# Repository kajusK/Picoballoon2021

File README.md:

Picoballoon Challenge 2021, Deadbadger probe
============================================

This probe was designed [Picoballoon Challenge](https://www.hvezdarna.cz/novinky/picoballoon-challenge-2021/)
organised by Brno Observatory and Planetarium. A goal of this competition
is to make a probe under 20 grams that would be launched on ballon to altitudes
around 5-15 km. Only requirement except weight is sending current altitude of the probe.

A detailed description is available at [deadbadger.cz](https://deadbadger.cz/projects/picoballoon-2021),
tracking site is at [bal.deadbadger.cz](https://bal.deadbadger.cz).

The probe contains
  * STM32F051 MCU
  * MS5607 Pressure and temperature sensor
  * Quectel L96 GPS module with integrated antenna
  * RFM95 LoRa Transceiver
  * MCP1640 based 3.3V boost regulator

Firmware
--------
As the commonly used [LMIC](https://github.com/matthijskooijman/arduino-lmic/tree/master/src)
library is quite bulky and far from perfect, I wrote my own LoRaWan library
inspired by [TinyLoRa](https://github.com/adafruit/TinyLoRa).

The main loop does about this:
  * Power up, initialize peripherals
  * Measure system voltages, pressure
  * Wait for GPS data or timeout
  * Power off GPS
  * Send data over LoRa (ABP, unconfirmed uplink)
  * Power off RFM95 trancesiver
  * Power off for 30 minutes
  * Repeat (GPS is powered on every 4th cycle)

Hardware
--------
The board was designed for 0.6 mm thick two sided PCB to reduce weight as
much as possible. Using thicker boards (usually 1.6 mm) changes the antenna
trace impedance, but it should not be that significant.

The programming and debug uart connectors are separated from the main layout
and this piece of the PCB will be snapped off before launch to reduce weight.

**Power consumption** with 3 V power supply
  * board topped at 50 mA with GPS searching for satellites, RFM in standby and MCU running
  * 7,3 mA with GPS powered off
  * 5,3 mA with RFM95 in sleep mode and GPS off
  * 45 uA with devices powered off

**Weight**
  * 10 g - Battery
  * ~3 g - Probe PCB with programming header
  * 12,39 g - Take off weight, officially measured

Frontend
--------
Data received by [TTN](https://www.thethingsnetwork.org/) are sent over
HTTP integration to custom web server that verifies the
auth header and stores data in sqlite database.

User frontend is written in python, it shows all received packets, flight route
and current position on a [map](https://api.mapy.cz).
The tracker is available at [bal.deadbadger](https://bal.deadbadger.cz)

To run the frontend in docker, run
```
docker build -t picoballon .
mkdir /srv/probe
touch /srv/probe/database.sqlite
# set token to use in auth header
echo "someuser:somepassword" > /srv/probe/token.txt
docker run -v /srv/probe/data:/project/cloud_data --mount type=bind,source=/srv/probe/database.sqlite,target=/project/database.sqlite --mount type=bind,source=/srv/probe/credentials.txt,target=/project/credentials.txt -p 8081:80 --name picoballon -d picoballon
```

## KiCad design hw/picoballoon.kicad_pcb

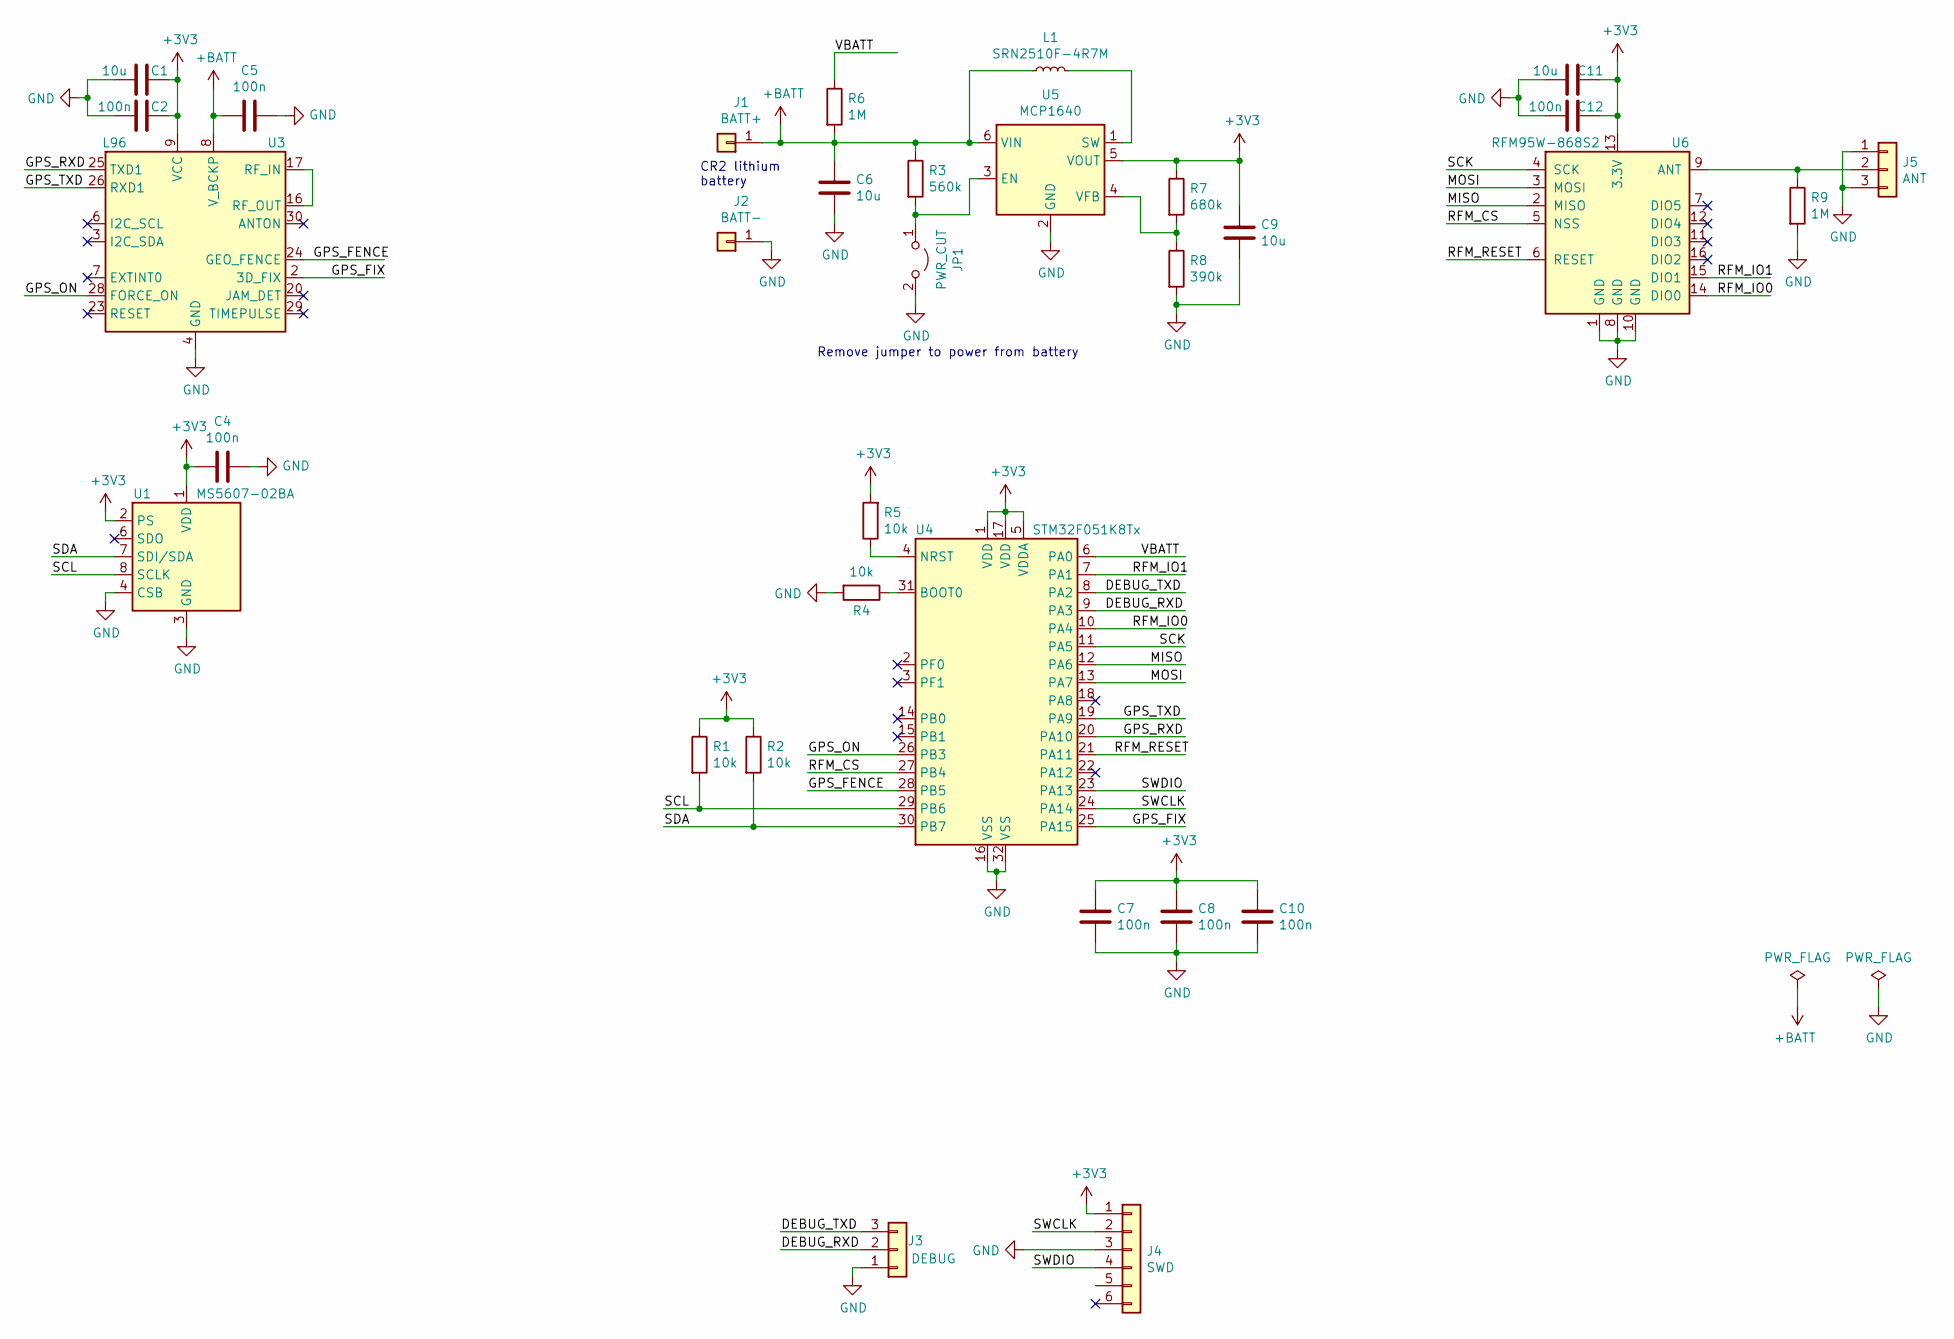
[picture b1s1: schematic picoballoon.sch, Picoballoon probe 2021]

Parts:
C1, C6, C9, C11: 10u; C_0603_1608Metric
C2, C4, C5, C7, C8, C10, C12: 100n; C_0603_1608Metric
J1: BATT+; PinSocket_1x01_P2.54mm_Vertical
J2: BATT-; PinHeader_1x01_P2.54mm_Vertical
J3: DEBUG; PinHeader_1x03_P2.54mm_Vertical
J4: SWD; PinHeader_2x03_P1.27mm_Vertical_SMD
J5: ANT; PinHeader_1x03_P2.54mm_Vertical
JP1: PWR_CUT; SolderJumper-2_P1.3mm_Open_Pad1.0x1.5mm
L1: SRN2510F-4R7M; L_Abracon_ASPI-3012S
R1, R2, R4, R5: 10k; R_0603_1608Metric
R3: 560k; R_0603_1608Metric
R6, R9: 1M; R_0603_1608Metric
R7: 680k; R_0603_1608Metric
R8: 390k; R_0603_1608Metric
U1: MS5607-02BA; LGA-8_3x5mm_P1.25mm
U3: L96; Quectel_L96
U4: STM32F051K8Tx; LQFP-32_7x7mm_P0.8mm
U5: MCP1640; SOT-23-6
U6: RFM95W-868S2; HOPERF_RFM9XW_SMD

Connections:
+3V3: C1.1, C2.1, C4.2, C7.1, C8.1, C9.1, C10.1, C11.1, C12.1, J4.1, R1.1, R2.1, R5.2, R7.1, U1.1 (VDD), U1.2 (PS), U3.9 (VCC), U4.1 (VDD), U4.5 (VDDA), U4.17 (VDD), U5.5 (VOUT), U6.13 (3.3V)
+BATT: C5.2, C6.1, J1.1, L1.1, R3.1, R6.2, U3.8 (V_BCKP), U3.23 (RESET), U5.6 (VIN)
/DEBUG_RXD: J3.2, U4.9 (PA3)
/DEBUG_TXD: J3.3, U4.8 (PA2)
/GPS_FENCE: U3.24 (GEO_FENCE), U4.28 (PB5)
/GPS_FIX: U3.2 (3D_FIX), U4.25 (PA15)
/GPS_ON: U3.28 (FORCE_ON), U4.26 (PB3)
/GPS_RXD: U3.25 (TXD1), U4.20 (PA10)
/GPS_TXD: U3.26 (RXD1), U4.19 (PA9)
/MISO: U4.12 (PA6), U6.2 (MISO)
/MOSI: U4.13 (PA7), U6.3 (MOSI)
/RFM_CS: U4.27 (PB4), U6.5 (NSS)
/RFM_IO0: U4.10 (PA4), U6.14 (DIO0)
/RFM_IO1: U4.7 (PA1), U6.15 (DIO1)
/RFM_RESET: U4.21 (PA11), U6.6 (RESET)
/SCK: U4.11 (PA5), U6.4 (SCK)
/SCL: R1.2, U1.8 (SCLK), U4.29 (PB6)
/SDA: R2.2, U1.7 (SDI/SDA), U4.30 (PB7)
/SWCLK: J4.2, U4.24 (PA14)
/SWDIO: J4.4, U4.23 (PA13)
/VBATT: R6.1, U4.6 (PA0)
GND: C1.2, C2.2, C4.1, C5.1, C6.2, C7.2, C8.2, C9.2, C10.2, C11.2, C12.2, J2.1, J3.1, J4.3, J5.1, J5.3, JP1.2 (B), R4.2, R8.2, R9.2, U1.3 (GND), U1.4 (CSB), U1.5 (CSB), U3.4 (GND), U3.5 (GND), U3.10 (GND), U3.11 (GND), U3.12 (GND), U3.13 (GND), U3.14 (GND), U3.15 (GND), U3.18 (GND), U3.19 (GND), U3.21 (GND), U3.22 (GND), U3.27 (GND), U3.31 (GND), U4.16 (VSS), U4.32 (VSS), U5.2 (GND), U6.1 (GND), U6.8 (GND), U6.10 (GND)
unnamed: J5.2, R9.1, U6.9 (ANT)
unnamed: JP1.1 (A), R3.2, U5.3 (EN)
unnamed: L1.2, U5.1 (SW)
unnamed: R4.1, U4.31 (BOOT0)
unnamed: R5.1, U4.4 (NRST)
unnamed: R7.2, R8.1, U5.4 (VFB)
unnamed: U3.16 (RF_OUT), U3.17 (RF_IN)

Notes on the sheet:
CR2 lithium battery
Remove jumper to power from battery

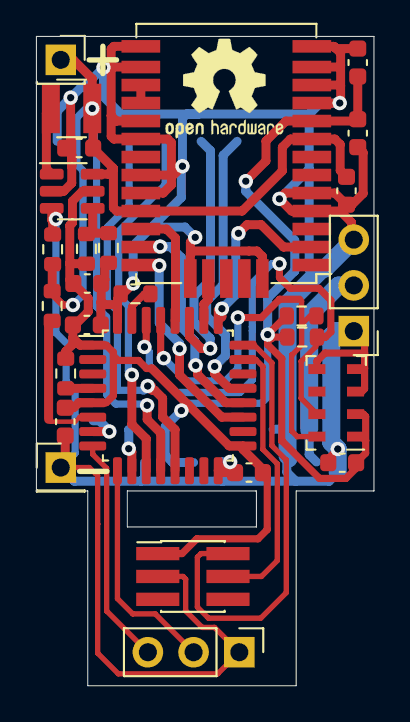
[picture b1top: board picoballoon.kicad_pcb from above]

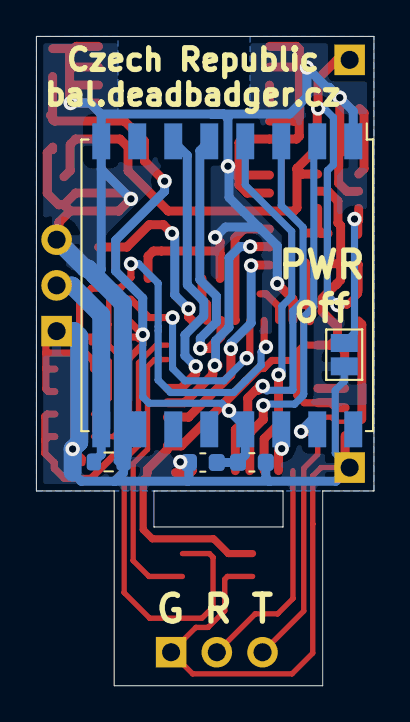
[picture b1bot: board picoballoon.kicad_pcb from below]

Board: 2 copper layers, 18.8 x 36.1 mm, 32 parts (5 on the bottom side), 29 nets.

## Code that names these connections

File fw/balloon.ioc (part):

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Mcu.Name=STM32F051K8Tx
Mcu.Package=LQFP32
Mcu.UserName=STM32F051K8Tx
PA0.GPIOParameters=GPIO_Label
PA0.GPIO_Label=VBATT
PA0.Mode=IN0
PA0.Signal=ADC_IN0
PA1.GPIOParameters=GPIO_PuPd,GPIO_Label
PA1.GPIO_Label=RFM_IO1
PA1.GPIO_PuPd=GPIO_PULLDOWN
PA1.Signal=GPIO_Input
PA10.GPIOParameters=GPIO_Label
PA10.GPIO_Label=GPS_RXD
PA10.Mode=Asynchronous
PA10.Signal=USART1_RX
PA11.GPIOParameters=GPIO_Label
PA11.GPIO_Label=RFM_RESET
PA11.Signal=GPIO_Output
PA12.Signal=GPIO_Analog
PA13.Mode=Serial_Wire
PA13.Signal=SYS_SWDIO
PA14.Mode=Serial_Wire
PA14.Signal=SYS_SWCLK
PA15.GPIOParameters=GPIO_PuPd,GPIO_Label
PA15.GPIO_Label=GPS_FIX
PA15.GPIO_PuPd=GPIO_PULLDOWN
PA15.Signal=GPIO_Input
PA2.GPIOParameters=GPIO_Label
PA2.GPIO_Label=DEBUG_TX
PA2.Mode=Asynchronous
PA2.Signal=USART2_TX
PA3.GPIOParameters=GPIO_Label
PA3.GPIO_Label=DEBUG_RX
PA3.Mode=Asynchronous
PA3.Signal=USART2_RX
PA4.GPIOParameters=GPIO_PuPd,GPIO_Label
PA4.GPIO_Label=RFM_IO0
PA4.GPIO_PuPd=GPIO_PULLDOWN
PA4.Signal=GPIO_Input
PA5.GPIOParameters=GPIO_PuPd
PA5.GPIO_PuPd=GPIO_PULLDOWN
PA5.Mode=Full_Duplex_Master
PA5.Signal=SPI1_SCK
PA6.GPIOParameters=GPIO_PuPd
PA6.GPIO_PuPd=GPIO_PULLDOWN
PA6.Mode=Full_Duplex_Master
PA6.Signal=SPI1_MISO
PA7.GPIOParameters=GPIO_PuPd
PA7.GPIO_PuPd=GPIO_PULLDOWN
PA7.Mode=Full_Duplex_Master
PA7.Signal=SPI1_MOSI
PA8.Signal=GPIO_Analog
PA9.GPIOParameters=GPIO_Label
PA9.GPIO_Label=GPS_TXD
PA9.Mode=Asynchronous
PA9.Signal=USART1_TX
PB0.Signal=GPIO_Analog
PB1.Signal=GPIO_Analog
PB3.GPIOParameters=GPIO_Label
PB3.GPIO_Label=GPS_ON
PB3.Signal=GPIO_Output
PB4.GPIOParameters=PinState,GPIO_Label
PB4.GPIO_Label=RFM_CS
PB4.PinState=GPIO_PIN_SET
PB4.Signal=GPIO_Output
PB5.GPIOParameters=GPIO_PuPd,GPIO_Label
PB5.GPIO_Label=GPS_FENCE
PB5.GPIO_PuPd=GPIO_PULLDOWN
PB5.Signal=GPIO_Input
PB6.Mode=I2C
PB6.Signal=I2C1_SCL
PB7.Mode=I2C
PB7.Signal=I2C1_SDA
PF0-OSC_IN.Signal=GPIO_Analog
PF1-OSC_OUT.Signal=GPIO_Analog
board=custom

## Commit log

2021-03-28 Added pcb design
2021-04-16 Initial firmware
2021-04-16 Added license and Readme
2021-04-23 Defined tx counter store address in linker
2021-05-09 core structure of frontend
2021-05-11 create database
2021-05-12 function endpoint, class Database in separate file db.py, create Readme
    Function database_status() checks if database.sqlite exists, if not, create one.
    Function endpoint() used for inserting data into database.
    Readme.db contains explanation of database structure.
2021-05-17 fixed creating Database instance, database attributes are now private
2021-05-17 creation of first tests
2021-05-18 added .gitignore, execute block into app.py, fixed test creating database
2021-05-22 Added TODO and tests description
2021-05-22 Rewrote the GPS timeouts and lora regions switching
2021-05-22 database path is configurable, progressing in tests of endpoint
2021-05-22 added flask context and temporary path to tests
2021-05-22 added fixtures for client and app
2021-05-22 creation of database inside class, method fetch data added
2021-05-22 function database_status removed
2021-05-22 removed test of database creation and added test of endpoint storing data
2021-05-24 added route to index.html, index contains map
    In app.py added route to index.html
    Index.html contains map centered on Brno (source: api.mapy.cz), with starting point on Brno Observatory
2021-05-25 Fixed ADC readings and sleep modes
2021-05-25 send data to markers and display them
    database instance from db.py fetch data for markers,
    index() in app.py send those data to index.html,
    which ultimately display markers with their cards to end user
2021-06-02 map can display markers using data from database
2021-06-04 display route of balloon on map
2021-06-05 latitude and longitude cannot be estimated
2021-06-05 add summary table
2021-06-07 incorporate bootstrap
    page is separated into 2 columns,
    the map has responsive size, is centered and zoomed to capture all markers, sizes of markers' cards are fixed
    sizes of the summary table and the image of probe are responsive
2021-06-07 split index() into 3 functions providing data for table, markers, graph
2021-06-07 format od database modified, deletion of redundant functions
2021-06-07 renaming variables, fix table (header text + center)
2021-06-13 finished design of page
2021-06-18 calculate altitude from pressure
2021-06-19 adapt database for real format of incoming data
2021-06-21 database can handle real format of data, tests are passing
2021-06-24 updated tests
2021-06-24 provide correct data to index
2021-06-24 change order of data
2021-06-24 correct json format
2021-06-24 table has fixed height and sticky header
2021-06-24 save data externally, pretty format function
2021-06-25 handle invalid input before passing to index.html
2021-06-25 treat 0 values as missing, fix identification of stronges gw
2021-06-25 more tests
2021-06-25 needless writing into file removed
2021-06-25 authorization added
2021-06-25 authorization added to tests
2021-06-25 picture of probe
2021-06-25 added frequency and rssi
2021-06-25 progess with graphs
2021-06-25 app can provide data to graphs
2021-06-25 values for database mustnt be strings
2021-06-25 more tests, better format
2021-06-25 readme updated
2021-06-25 debug disabled
2021-06-26 endpoint handles invalid incoming data
2021-06-26 database path is configurable, more tests
2021-06-26 database functions' names changed
2021-06-26 adapt database, app and tests for real format of incoming data
2021-06-26 more tests, better format of data sent to index
2021-06-26 added frequency and rssi into database
2021-06-26 progress with graphs
2021-06-26 object of database serves for one job, tests adapted
2021-06-27 Changed default pin states to (hopefully) reduce power consumption
2021-06-27 Reducing power consumption, updated region switching logic
2021-06-27 Added notes for future board revisions
2021-06-27 Fixed typo in config
2021-06-27 Added docker file for tracker
2021-06-27 Updated probe image and webpage description
2021-06-27 db instances fixed, directory for cloud data + readable json names
2021-06-27 height of table fixed
2021-06-27 Fixed auth header format and unit tests
2021-06-27 fix temperature handling, fix tests authorization
2021-06-27 frontend rework
2021-06-27 Send pressure in Pa
2021-06-28 fixes - db can correctly save strongest gw with coordinates - index - altitude in header - app - function upload_data to extract data into database from raw .txt
2021-06-29 Added official take off weight
2021-06-29 Update from jsons when -u is passed
